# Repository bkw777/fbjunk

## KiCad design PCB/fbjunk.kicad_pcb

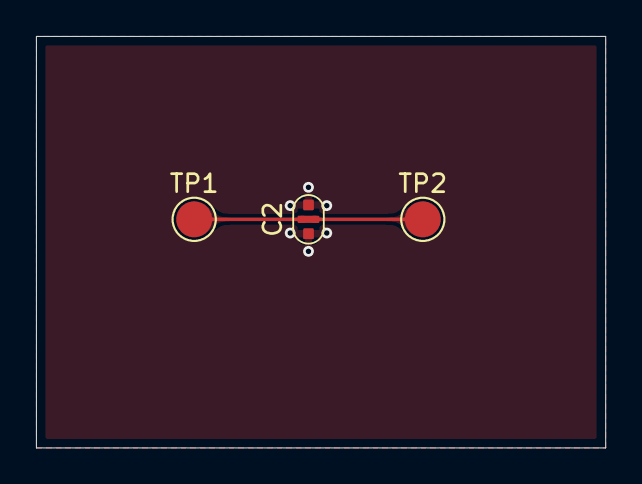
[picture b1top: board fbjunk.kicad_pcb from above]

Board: 2 copper layers, 31.6 x 22.9 mm, 3 parts (0 on the bottom side), 2 nets.

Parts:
C2: C_Feedthrough_CUSTOM_HACK; C_0603_FeedThrough
TP1, TP2: TestPoint; TestPoint_Pad_D2.0mm

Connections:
+12V: C2.2, TP1.1, TP2.1
GND: C2.1, C2.3

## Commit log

2025-11-21 initial
2025-11-21 fix footprint pin 2
2025-11-21 add hack inverted pinout symbol
2026-01-13 kicad library xiao 23p
2026-01-13 xiao lib path
2026-01-13 organize
